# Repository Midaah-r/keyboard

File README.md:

# keyboard

- compact & sleek
- 66x keys!
- Tweaked 65% layout
- 1x EC11 Rotary Encoder - For Volume, Brightness, etc
- powered by rp pico
- KMK firmware
- WOBBLY WIGGLY silkscreen

## Description

This is my first project of this scale and it was an amazing experience building this, i got to learn a lot! 

I would like to thank hackclub's hackapad tutorial, Joe Scotto and Google, you guys were my saviors.

The keyboard is a tweaked default 65% layout with one key replaced by a RE. The MCU used is Raspberry Pi Pico and the firmware used is kmk.

layout:

<image src="assets_journal/layout.png" width="400">

## PCB

**Dimensions**: 307mm x 125mm
Made inside of Kicad

| Schematic                 |
| ------------------------- |
|  |

| Pcb                 |
| --------------------- |
|  |

| Assembled - front             |
| ------------------------ |
|  |

| Assembled - Back               |
| ----------------------- |
|  |

## Case

The case was made in Fusion360.

bottom:

plate:

top:

## Assembly:

## Port: 

## BOM

| Name                                                                  | Qty | Final Price - INR (USD) | Link                                                                                                                |
| --------------------------------------------------------------------- | --- | ----------------------- | ------------------------------------------------------------------------------------------------------------------- |
| Gateron EF Grayish                                                    | 80  | 1560 ($17.79)           | [here](https://neomacro.in/products/gateron-ef-grayish)                                                             |
| Cherry Profile PBT Keycaps                                            | 1   | 1299 ($14.81)           | [here](https://stackskb.com/store/veekos-gradient-keycaps-cherry-profile-135-keys/)                                 |
| Durock Smokey Screw-In Stabilizers V2 (4+1 w/ 6.25u spacebar)         | 1   | 1595 ($18.18)           | [here](https://stackskb.com/store/durock-smokey-screw-in-stabilizers-v2/)                                           |
| Diode 1N4148 Through - Hole                                           | 80  | 176 ($2.01)             | [here](https://roboticsdna.in/product/diode-1n4148/)                                                                |
| EC11 Rotary Encoder                                                   | 2   | 178 ($2.03)             | [here](https://amzn.in/d/hVRxzij)                                                                                   |
| M3 x 16mm Allen Bolt                                                  | 25  | 170 ($1.94)             | [here](https://www.amazon.in/RT-SENSE-Socket-Screws-Machine/dp/B0CX999P9J?crid=2LR651EVK17U6&dib=eyJ2IjoiMSJ9.pNwgmpLhpW7wMwHM-KbUxGVZIEWQ2PGyzOzppZaKMsH_eIl0XoWwObHuOTBQY-qZBu8ZQUnJfckAdPsG8raXK7qR8XB8MCC0i2wtfO1oT-nOePOt5mxRUj8Ucb9E33RXC6qDRZnypdXQTVkdquX1Q0ZcLuifCMFaAYO2HtIUq_JIllvDGxRuvqQ3c-rZqzXCEkMEDP47IOF2iwhRIUPUw57NAhduxtgZALv13CXXj4YBPeHcs29PGndT0i9IRJUeifo_HE2IIZ4FttYTmnpoowtiYnSRvn9NrZaGp0pjE2g.847NW6XZvS4t8iLKZyZfb2ihLqAsqOKPYnZJtFc3xyY&dib_tag=se&keywords=16mm%2Bscrew%2Ballen%2Bsocket%2Bm3&qid=1753889826&s=industrial&sprefix=16%2Bmm%2Bscrew%2Ballen%2Bsocket%2Bm3%2Cindustrial%2C256&sr=1-3&th=1) |
| M3 x 8mm Allen Bolt                                                   | 15  | 150 ($1.71)             | [here](https://www.amazon.in/RT-SENSE-Socket-Screws-Machine/dp/B0CX99XY91?crid=2AAVLRC2YKK5N&dib=eyJ2IjoiMSJ9.HGL6-0P5xO7QNC1ET0QVTqcjke85LzZ_hZFkE2FxStoyveDWcFTfmB0PbzocM9bLWFFNLuquRZevBamMDVv6f7dpj7wOrbBJBK2zKs-6mCrW48gMHICHbG_rYhk9p8f5-AuC5J7DMCQ-VZLxf9VF3ClZtXbCIfD-SNrdKhb3ctDg0MupFs3SLgcjo4KVJgbxcUZAjDfx_lG9zSqqlKLNb2Yo6DbtxAxZHNhLK5SwI8_hxLkeFY3v3M7xlaZVwBZkrNpkir422zl5ziZhtALxuxa8Tbmn16RyfBFr6-S-5LQ.WTUDRTVHWxEiKPkCARjbkRHYKSXbn3eUCPpKHZpgQZ8&dib_tag=se&keywords=8mm%2Bscrew%2Ballen%2Bsocket%2Bm3&qid=1753889576&s=industrial&sprefix=8mm%2Bscrew%2Ballen%2Bsocket%2Bm%2Cindustrial%2C245&sr=1-5&th=1)       |
| M3 x 6mm Heatset Insert                                               | 12  | 100 ($1.14)             | [here](https://www.amazon.in/M3X6-Brass-Threaded-Round-Insert/dp/B0BB86CQSJ?crid=YYANQYUOPD4W&dib=eyJ2IjoiMSJ9.MemffQEv6bwN_JwUkjgflx4yIYhqm-RoBde59N0L6lAgMFwLuFXhTXzs0eDDDvillLCmvl9utxXvY49WkAfGcItHt6VeuPsJ9drtoxcmQGmNNcx1gavKHQunp5kw-RVbB5WgNUFQevQtkmyaHbSWSzZThYkrD4e64ZsYjEgj-ymPEzco9HdNRo16uPFU9F_OxiM3ed33wdClqKYUYyssQtOqYRFBF7eAdcrUMvf5zj9zd2SifrZUKiiOJZKEtIcVPqFy1BMa-mAQNq5PcKpe-ZDoQjop59g2b8F_UQIG7RM.hOB7rRGhO36946nYdxL4EXpyM_xdgFSJlnxi1Mm52lM&dib_tag=se&keywords=m3+4mm+heatset+inserts&qid=1753889984&s=industrial&sprefix=m3+4mm+heatset+inserts%2Cindustrial%2C212&sr=1-2)                                 |
| Raspberry Pi Pico                                                     | 1   | 384 ($4.38)             | [here](https://roboticsdna.in/product/raspberry-pi-pico/)                                                           |
| Micro usb to type A cable                                             | 2   | 580 ($6.62)             | [here](https://www.amazon.in/amazon-basics-Braided-Charging-Transfer/dp/B0CH14KT9N?crid=7ZGZL0SGL62I&dib=eyJ2IjoiMSJ9.54pQ4hLP-x3QnLhOqkaGTy7rI5nnFnLYF-313TPM28L18X6r5ZCKEbeYkPNGO9xsBzB6A0knLau59HoH5s8y2_oozITo2lsVxj1CJAevJEhkgUtv_yfu0JsiZI1iWCJ_qfU07G3d2w5jV-JRmyCr0ZvmLtZVdnDna6yZQvqUs-UeQhuhdCSRuxgoQx3Ouvc-hEGrl-8z2HmKTjhQsAG4FZivKGkkLwcdb7KxPxWw66I.1HTltbJMC5n1amEKrnUqS-67AznIHpVUr3XIcqJ_iXE&dib_tag=se&keywords=micro%2Busb%2Bto%2Ba&qid=1753927324&sprefix=micro%2Busb%2Bto%2Ba%2Caps%2C279&sr=8-3&th=1)                                                                                                                 |
| 4 in 1 USB hub                                                        | 1   | 200 ($2.28)             | [here](https://www.amazon.in/Amazon-Multiport-Adapter-Aluminium-MacBook/dp/B0CFLT45KH?crid=1AVZO6HJY7GKW&dib=eyJ2IjoiMSJ9.SbvLUcslbfZTFiES8rrCw2Nwiq7-hwNIM1JJEtVWqKmVIHD0xINbChtPw96BH1Z7bwAQvg7WEo0FLIj5NjPNZV3HESwG84oN9MGwFF_ktYWZFGq2_zIgHYh0_s8JsbwBZUuOctIL-YbY-ORDviNg51orED6FDcbN4kU47Yrz4v_sdHkRenj7_NzQM-dblPKtJCT0zWr3maz6kzoE8fH5MXkfG0hqnJWIndJLs4MHuFk.Wps7TnRlfHtjdMeHHtPgy7cId7XVHc2PYy59TEg0SXQ&dib_tag=se&keywords=usb+hub&qid=1753928115&sprefix=usb+hu%2Caps%2C246&sr=8-4)                                                                                                                                                 |
| Lube (silicon dielectric grease)                                      | 1   | 270 ($3.1)              | [here](https://www.amazon.in/gp/product/B08R3NXT3B?smid=AYQOQ4F60DJ09&th=1)                                         |
| PCB (White)                                                           | 5   | 4136.45 ($47.2)         | [from jlcpcb](assets/jlcpcb_quote.png)                                                                              | 
| Middle plate - 1 (White "production/MIDDLE.step")                     | 1   | 1276 ($14.56)           | [from 3ding.in](assets/3ding_quote.png)                                                                             |
| Bottom Case - 1 (White "production/BOTTOM.step")                      | 1   | Print Legion            |
| Top Case - 1 (White "production/TOP.step")                            | 1   | Print Legion            |
| Rotary Encoder Knob                                                   | 1   | Print Legion            |
| Shipping (for diodes, MCU and Amazon)                                 | -   | 260.06 ($3)             |

## Grand Total

The total sum of the parts comes to approximately inr 12335 ($141.5).

I have chosen air registered mail as the shipping option for jlcpcb as it's less likely to incurr customs thus actually being cheaper than other shipping providers.

PS: i have also included an additional USB hub and 2 microusb to type A cables because of the macropad and keyboard i wont have any space to plug the gadgets into my laptop

> **Note:** TOP and BOTTOM case parts in white, MIDDLE in black; PCB must be white.

Some componenets were ordered in packs due to unavailability (bolts, heatset inserts, etc), their prices may vary due to sales.

The final quote is subject to dollar-market trends

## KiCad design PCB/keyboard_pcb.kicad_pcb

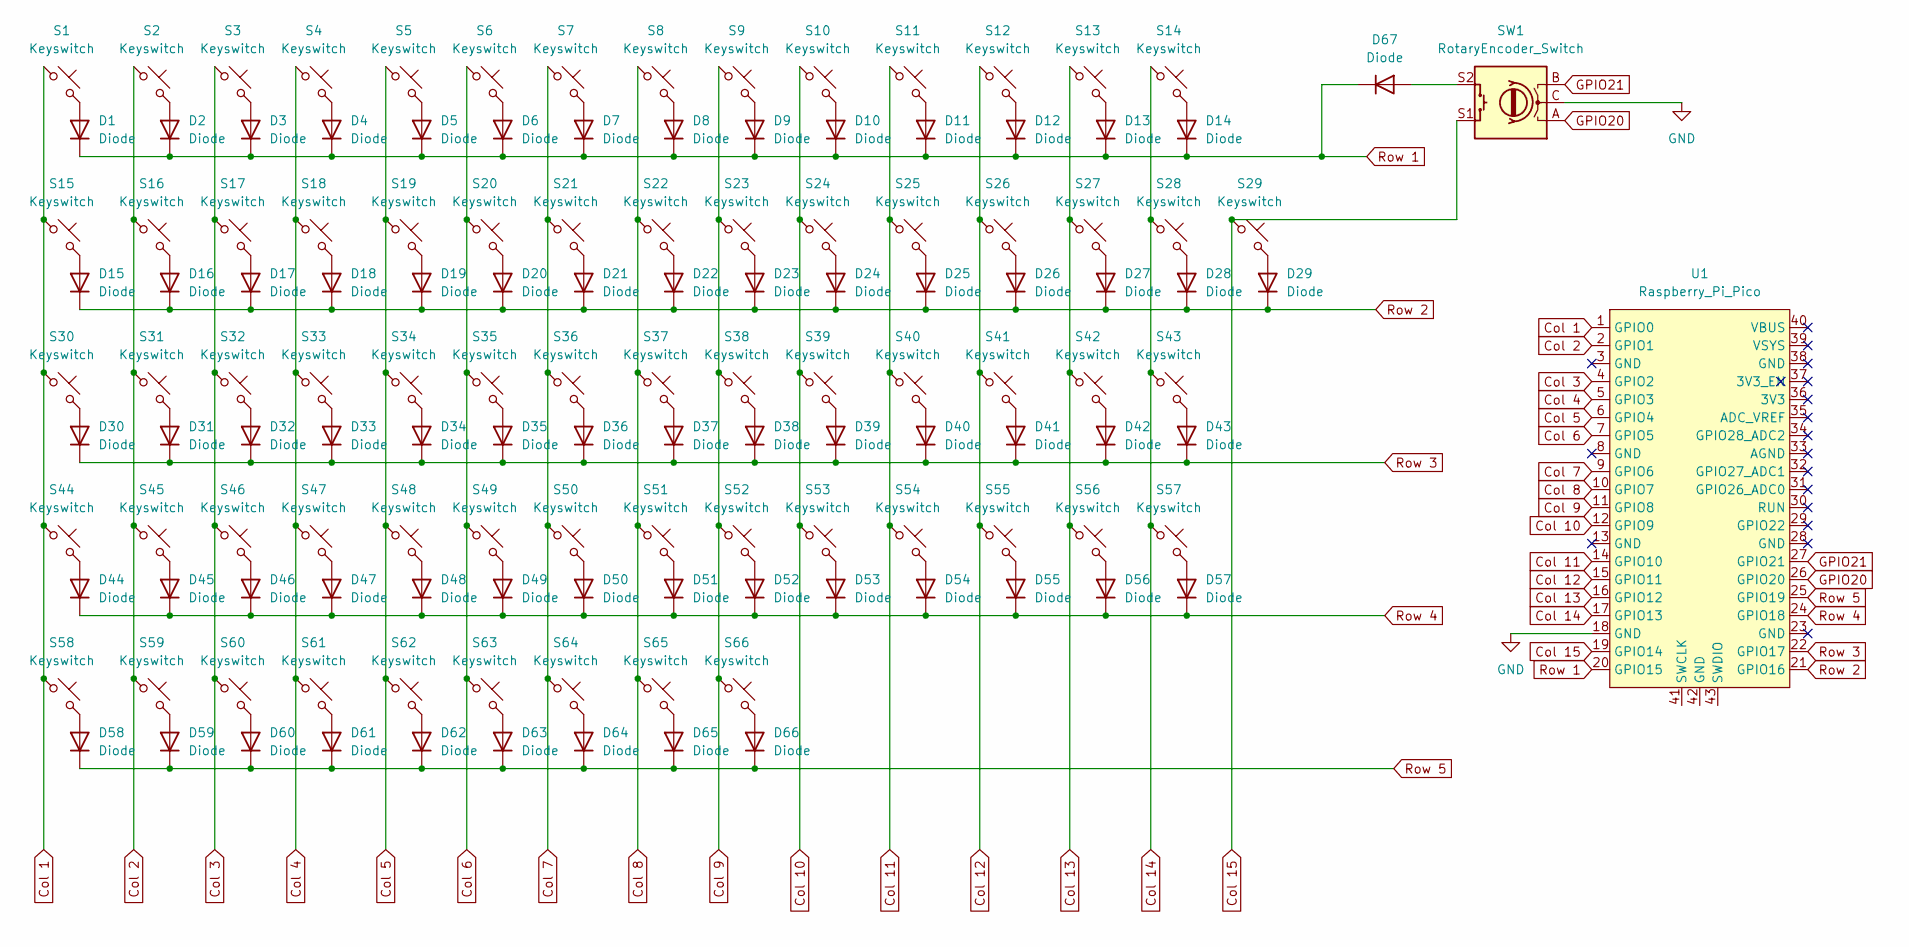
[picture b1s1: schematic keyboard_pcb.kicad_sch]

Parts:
D1, D2, D3, D4, D5, D6, D7, D8, D9, D10, D11, D12, D13, D14, D15, D16, D17, D18, D19, D20, D21, D22, D23, D24, D25, D26, D27, D28, D29, D30, D31, D32, D33, D34, D35, D36, D37, D38, D39, D40, D41, D42, D43, D44, D45, D46, D47, D48, D49, D50, D51, D52, D53, D54, D55, D56, D57, D58, D59, D60, D61, D62, D63, D64, D65, D66, D67: Diode; Diode_DO-35
S1, S2, S3, S4, S5, S6, S7, S8, S9, S10, S11, S12, S13, S16, S17, S18, S19, S20, S21, S22, S23, S24, S25, S26, S27, S29, S31, S32, S33, S34, S35, S36, S37, S38, S39, S40, S41, S43, S45, S46, S47, S48, S49, S50, S51, S52, S53, S54, S56, S57, S64, S65, S66: Keyswitch; MX_PCB_1.00u
S14: Keyswitch; SW_Cherry_MX_2.00u_PCB
S15, S28: Keyswitch; MX_PCB_1.50u
S30, S55: Keyswitch; MX_PCB_1.75u
S42, S44: Keyswitch; SW_Cherry_MX_2.25u_PCB
S58, S59, S60, S62, S63: Keyswitch; MX_PCB_1.25u
S61: Keyswitch; SW_Cherry_MX_6.25u_PCB
SW1: RotaryEncoder_Switch; RotaryEncoder_Alps_EC11E-Switch_Vertical_H20mm
U1: Raspberry_Pi_Pico

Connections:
Col 1: S1.1, S15.1, S30.1, S44.1, S58.1, U1.1 (GPIO0)
Col 2: S2.1, S16.1, S31.1, S45.1, S59.1, U1.2 (GPIO1)
Col 3: S3.1, S17.1, S32.1, S46.1, S60.1, U1.4 (GPIO2)
Col 4: S4.1, S18.1, S33.1, S47.1, S61.1, U1.5 (GPIO3)
Col 5: S5.1, S19.1, S34.1, S48.1, S62.1, U1.6 (GPIO4)
Col 6: S6.1, S20.1, S35.1, S49.1, S63.1, U1.7 (GPIO5)
Col 7: S7.1, S21.1, S36.1, S50.1, S64.1, U1.9 (GPIO6)
Col 8: S8.1, S22.1, S37.1, S51.1, S65.1, U1.10 (GPIO7)
Col 9: S9.1, S23.1, S38.1, S52.1, S66.1, U1.11 (GPIO8)
Col 10: S10.1, S24.1, S39.1, S53.1, U1.12 (GPIO9)
Col 11: S11.1, S25.1, S40.1, S54.1, U1.14 (GPIO10)
Col 12: S12.1, S26.1, S41.1, S55.1, U1.15 (GPIO11)
Col 13: S13.1, S27.1, S42.1, S56.1, U1.16 (GPIO12)
Col 14: S14.1, S28.1, S43.1, S57.1, U1.17 (GPIO13)
Col 15: S29.1, SW1.S1, U1.19 (GPIO14)
GND: SW1.C, U1.18 (GND)
GPIO20: SW1.A, U1.26 (GPIO20)
GPIO21: SW1.B, U1.27 (GPIO21)
unnamed: D1.2 (A), S1.2
unnamed: D2.2 (A), S2.2
unnamed: D3.2 (A), S3.2
unnamed: D4.2 (A), S4.2
unnamed: D5.2 (A), S5.2
unnamed: D6.2 (A), S6.2
unnamed: D7.2 (A), S7.2
unnamed: D8.2 (A), S8.2
unnamed: D9.2 (A), S9.2
unnamed: D10.2 (A), S10.2
unnamed: D11.2 (A), S11.2
unnamed: D12.2 (A), S12.2
unnamed: D13.2 (A), S13.2
unnamed: D14.2 (A), S14.2
unnamed: D15.2 (A), S15.2
unnamed: D16.2 (A), S16.2
unnamed: D17.2 (A), S17.2
unnamed: D18.2 (A), S18.2
unnamed: D19.2 (A), S19.2
unnamed: D20.2 (A), S20.2
unnamed: D21.2 (A), S21.2
unnamed: D22.2 (A), S22.2
unnamed: D23.2 (A), S23.2
unnamed: D24.2 (A), S24.2
unnamed: D25.2 (A), S25.2
unnamed: D26.2 (A), S26.2
unnamed: D27.2 (A), S27.2
unnamed: D28.2 (A), S28.2
unnamed: D29.2 (A), S29.2
unnamed: D30.2 (A), S30.2
unnamed: D31.2 (A), S31.2
unnamed: D32.2 (A), S32.2
unnamed: D33.2 (A), S33.2
unnamed: D34.2 (A), S34.2
unnamed: D35.2 (A), S35.2
unnamed: D36.2 (A), S36.2
unnamed: D37.2 (A), S37.2
unnamed: D38.2 (A), S38.2
unnamed: D39.2 (A), S39.2
unnamed: D40.2 (A), S40.2
unnamed: D41.2 (A), S41.2
unnamed: D42.2 (A), S42.2
unnamed: D43.2 (A), S43.2
unnamed: D44.2 (A), S44.2
unnamed: D45.2 (A), S45.2
unnamed: D46.2 (A), S46.2
unnamed: D47.2 (A), S47.2
unnamed: D48.2 (A), S48.2
unnamed: D49.2 (A), S49.2
unnamed: D50.2 (A), S50.2
unnamed: D51.2 (A), S51.2
unnamed: D52.2 (A), S52.2
unnamed: D53.2 (A), S53.2
unnamed: D54.2 (A), S54.2
unnamed: D55.2 (A), S55.2
unnamed: D56.2 (A), S56.2
unnamed: D57.2 (A), S57.2
unnamed: D58.2 (A), S58.2
unnamed: D59.2 (A), S59.2
unnamed: D60.2 (A), S60.2
unnamed: D61.2 (A), S61.2
unnamed: D62.2 (A), S62.2
unnamed: D63.2 (A), S63.2
unnamed: D64.2 (A), S64.2
unnamed: D65.2 (A), S65.2
unnamed: D66.2 (A), S66.2
unnamed: D67.2 (A), SW1.S2
Row 1: D1.1 (K), D2.1 (K), D3.1 (K), D4.1 (K), D5.1 (K), D6.1 (K), D7.1 (K), D8.1 (K), D9.1 (K), D10.1 (K), D11.1 (K), D12.1 (K), D13.1 (K), D14.1 (K), D67.1 (K), U1.20 (GPIO15)
Row 2: D15.1 (K), D16.1 (K), D17.1 (K), D18.1 (K), D19.1 (K), D20.1 (K), D21.1 (K), D22.1 (K), D23.1 (K), D24.1 (K), D25.1 (K), D26.1 (K), D27.1 (K), D28.1 (K), D29.1 (K), U1.21 (GPIO16)
Row 3: D30.1 (K), D31.1 (K), D32.1 (K), D33.1 (K), D34.1 (K), D35.1 (K), D36.1 (K), D37.1 (K), D38.1 (K), D39.1 (K), D40.1 (K), D41.1 (K), D42.1 (K), D43.1 (K), U1.22 (GPIO17)
Row 4: D44.1 (K), D45.1 (K), D46.1 (K), D47.1 (K), D48.1 (K), D49.1 (K), D50.1 (K), D51.1 (K), D52.1 (K), D53.1 (K), D54.1 (K), D55.1 (K), D56.1 (K), D57.1 (K), U1.24 (GPIO18)
Row 5: D58.1 (K), D59.1 (K), D60.1 (K), D61.1 (K), D62.1 (K), D63.1 (K), D64.1 (K), D65.1 (K), D66.1 (K), U1.25 (GPIO19)

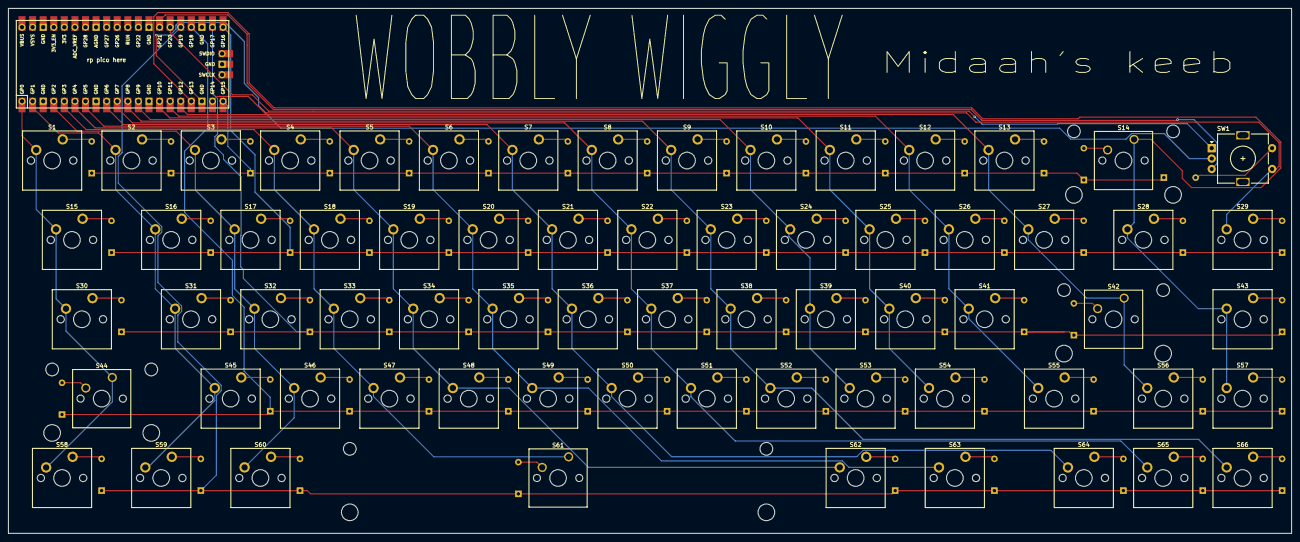
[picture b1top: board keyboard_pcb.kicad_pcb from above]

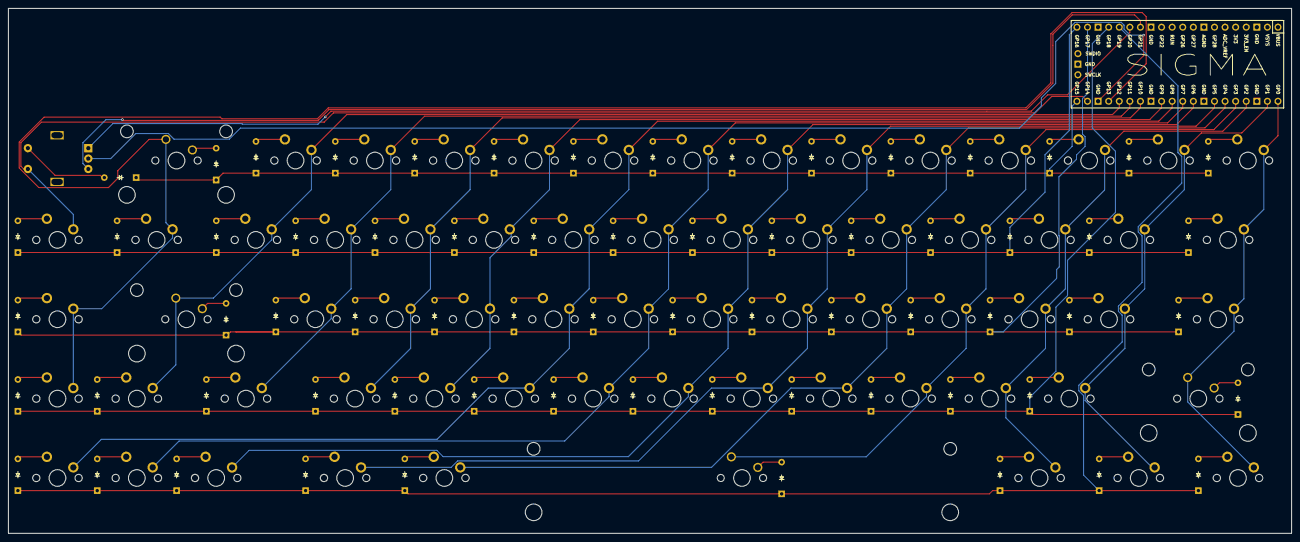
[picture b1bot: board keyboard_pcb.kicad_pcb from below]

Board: 2 copper layers, 308.0 x 126.0 mm, 135 parts (67 on the bottom side), 90 nets.

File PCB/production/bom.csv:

Designator,Footprint,Quantity,Value,LCSC Part #
"D1, D10, D11, D12, D13, D14, D15, D16, D17, D18, D19, D2, D20, D21, D22, D23, D24, D25, D26, D27, D28, D29, D3, D30, D31, D32, D33, D34, D35, D36, D37, D38, D39, D4, D40, D41, D42, D43, D44, D45, D46, D47, D48, D49, D5, D50, D51, D52, D53, D54, D55, D56, D57, D58, D59, D6, D60, D61, D62, D63, D64, D65, D66, D67, D7, D8, D9",Diode_DO-35,67,Diode,
"S1, S10, S11, S12, S13, S16, S17, S18, S19, S2, S20, S21, S22, S23, S24, S25, S26, S27, S29, S3, S31, S32, S33, S34, S35, S36, S37, S38, S39, S4, S40, S41, S43, S45, S46, S47, S48, S49, S5, S50, S51, S52, S53, S54, S56, S57, S6, S64, S65, S66, S7, S8, S9",MX_PCB_1.00u,53,Keyswitch,
S14,SW_Cherry_MX_2.00u_PCB,1,Keyswitch,
"S15, S28",MX_PCB_1.50u,2,Keyswitch,
"S30, S55",MX_PCB_1.75u,2,Keyswitch,
"S42, S44",SW_Cherry_MX_2.25u_PCB,2,Keyswitch,
"S58, S59, S60, S62, S63",MX_PCB_1.25u,5,Keyswitch,
S61,SW_Cherry_MX_6.25u_PCB,1,Keyswitch,
SW1,RotaryEncoder_Alps_EC11E-Switch_Vertical_H20mm,1,RotaryEncoder_Switch,
U1,Raspberry_Pi_Pico,1,Raspberry_Pi_Pico,

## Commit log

2025-07-27 added day 1 info
2025-07-29 added day 2 entry
2025-07-29 formatting
2025-07-30 added day 3 entry
2025-07-30 re: added day 3 entry
2025-07-30 fixed typos
2025-07-30 fixed minor errors JOURNAL.md
    typed jpg instead of png. im tired today....
2025-07-31 added CAD, production, PCB, assets and day4 of journal
2025-07-31 added temporary firmware
2025-07-31 Added BOM.csv
2025-07-31 README typos
2025-07-31 added total time spent
2025-07-31 Updated BOM
2025-08-01 Added day 5 and 6 entry along with assets
2025-08-01 fixed readme
2025-08-01 fixed journal
2025-08-01 Made final changes to CAD, production and added new assets
2025-08-02 updated BOM for shipping
2025-08-03 update BOM
2025-08-12 updated pcb related folders/files and added journal entry
2025-08-12 updated journal
2025-08-14 updated JOURNAL.md
